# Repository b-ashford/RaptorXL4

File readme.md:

# RaptorXL4  

RaptorXL4 is a custom breakout board I designed to prototype the [Auto-Tuner](https://github.com/b-ashford/Auto-Tuner).  
It’s built around the **STM32L431CBT6** and includes:  

- 24 MHz HSE crystal  
- On-board ST-LINK–compatible programmer/debugger  
- User LED for quick “blinky” tests  
- VDDA supply with ferrite bead filtering for cleaner ADC performance  
- Access to most MCU pins for prototyping  
- Cool raptor silkscreen

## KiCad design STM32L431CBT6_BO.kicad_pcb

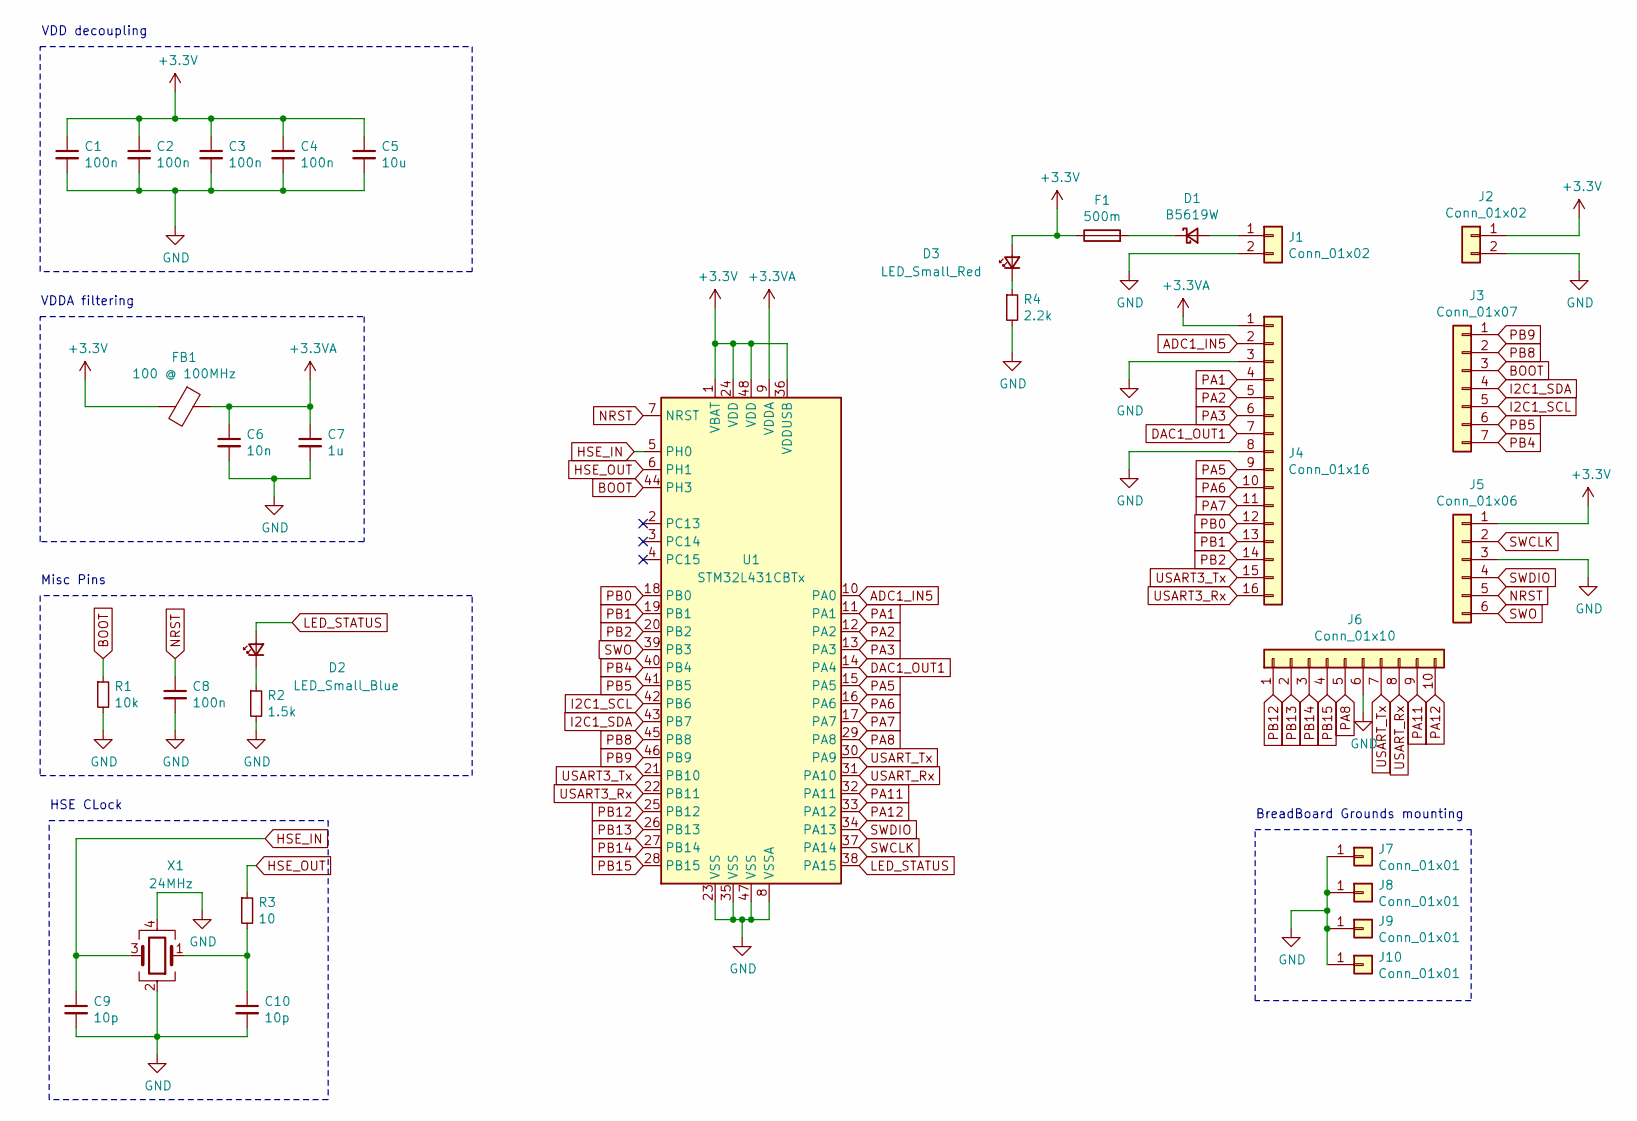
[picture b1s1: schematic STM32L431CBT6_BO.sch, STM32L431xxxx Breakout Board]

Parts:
C1, C2, C3, C4, C8: 100n; C_0402_1005Metric_Pad0.74x0.62mm_HandSolder
C5: 10u; C_0603_1608Metric_Pad1.08x0.95mm_HandSolder
C6: 10n; C_0402_1005Metric_Pad0.74x0.62mm_HandSolder
C7: 1u; C_0603_1608Metric_Pad1.08x0.95mm_HandSolder
C9, C10: 10p; C_0402_1005Metric_Pad0.74x0.62mm_HandSolder
D1: B5619W; D_SOD-123
D2: LED_Small_Blue; LED_0603_1608Metric_Pad1.05x0.95mm_HandSolder
D3: LED_Small_Red; LED_0603_1608Metric_Pad1.05x0.95mm_HandSolder
F1: 500m; Fuse_0603_1608Metric_Pad1.05x0.95mm_HandSolder
FB1: 100 @ 100MHz; L_0805_2012Metric_Pad1.05x1.20mm_HandSolder
J1, J2: Conn_01x02; PinHeader_1x02_P2.54mm_Vertical
J3: Conn_01x07; PinHeader_1x07_P2.54mm_Vertical
J4: Conn_01x16; PinHeader_1x16_P2.54mm_Vertical
J5: Conn_01x06; PinHeader_1x06_P2.54mm_Vertical
J6: Conn_01x10; PinHeader_1x10_P2.54mm_Vertical
J7, J8, J9, J10: Conn_01x01; PinHeader_1x01_P2.54mm_Vertical
R1: 10k; R_0402_1005Metric_Pad0.72x0.64mm_HandSolder
R2: 1.5k; R_0603_1608Metric_Pad0.98x0.95mm_HandSolder
R3: 10; R_0402_1005Metric_Pad0.72x0.64mm_HandSolder
R4: 2.2k; R_0603_1608Metric_Pad0.98x0.95mm_HandSolder
U1: STM32L431CBTx; LQFP-48_7x7mm_P0.5mm
X1: 24MHz; Crystal_SMD_3225-4Pin_3.2x2.5mm_HandSoldering

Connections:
+3.3VA: C6.1, C7.1, FB1.1, J4.1, U1.9 (VDDA)
+3V3: C1.1, C2.1, C3.1, C4.1, C5.1, D3.2 (A), F1.1, FB1.2, J2.1, J5.1, U1.1 (VBAT), U1.24 (VDD), U1.36 (VDDUSB), U1.48 (VDD)
ADC1_IN5: J4.2, U1.10 (PA0)
BOOT: J3.3, R1.1, U1.44 (PH3)
DAC1_OUT1: J4.7, U1.14 (PA4)
GND: C1.2, C2.2, C3.2, C4.2, C5.2, C6.2, C7.2, C8.2, C9.2, C10.2, J1.2, J2.2, J4.3, J4.8, J5.3, J6.6, J7.1, J8.1, J9.1, J10.1, R1.2, R2.2, R4.2, U1.8 (VSSA), U1.23 (VSS), U1.35 (VSS), U1.47 (VSS), X1.2, X1.4
HSE_IN: C9.1, U1.5 (PH0), X1.3
HSE_OUT: R3.1, U1.6 (PH1)
I2C1_SCL: J3.5, U1.42 (PB6)
I2C1_SDA: J3.4, U1.43 (PB7)
LED_STATUS: D2.2 (A), U1.38 (PA15)
NRST: C8.1, J5.5, U1.7 (NRST)
unnamed: C10.1, R3.2, X1.1
unnamed: D1.1 (K), F1.2
unnamed: D1.2 (A), J1.1
unnamed: D2.1 (K), R2.1
unnamed: D3.1 (K), R4.1
PA1: J4.4, U1.11 (PA1)
PA2: J4.5, U1.12 (PA2)
PA3: J4.6, U1.13 (PA3)
PA5: J4.9, U1.15 (PA5)
PA6: J4.10, U1.16 (PA6)
PA7: J4.11, U1.17 (PA7)
PA8: J6.5, U1.29 (PA8)
PA11: J6.9, U1.32 (PA11)
PA12: J6.10, U1.33 (PA12)
PB0: J4.12, U1.18 (PB0)
PB1: J4.13, U1.19 (PB1)
PB2: J4.14, U1.20 (PB2)
PB4: J3.7, U1.40 (PB4)
PB5: J3.6, U1.41 (PB5)
PB8: J3.2, U1.45 (PB8)
PB9: J3.1, U1.46 (PB9)
PB12: J6.1, U1.25 (PB12)
PB13: J6.2, U1.26 (PB13)
PB14: J6.3, U1.27 (PB14)
PB15: J6.4, U1.28 (PB15)
SWCLK: J5.2, U1.37 (PA14)
SWDIO: J5.4, U1.34 (PA13)
SWO: J5.6, U1.39 (PB3)
USART3_Rx: J4.16, U1.22 (PB11)
USART3_Tx: J4.15, U1.21 (PB10)
USART_Rx: J6.8, U1.31 (PA10)
USART_Tx: J6.7, U1.30 (PA9)

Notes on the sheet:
HSE CLock
VDD decoupling
VDDA filtering
Misc Pins
BreadBoard Grounds mounting

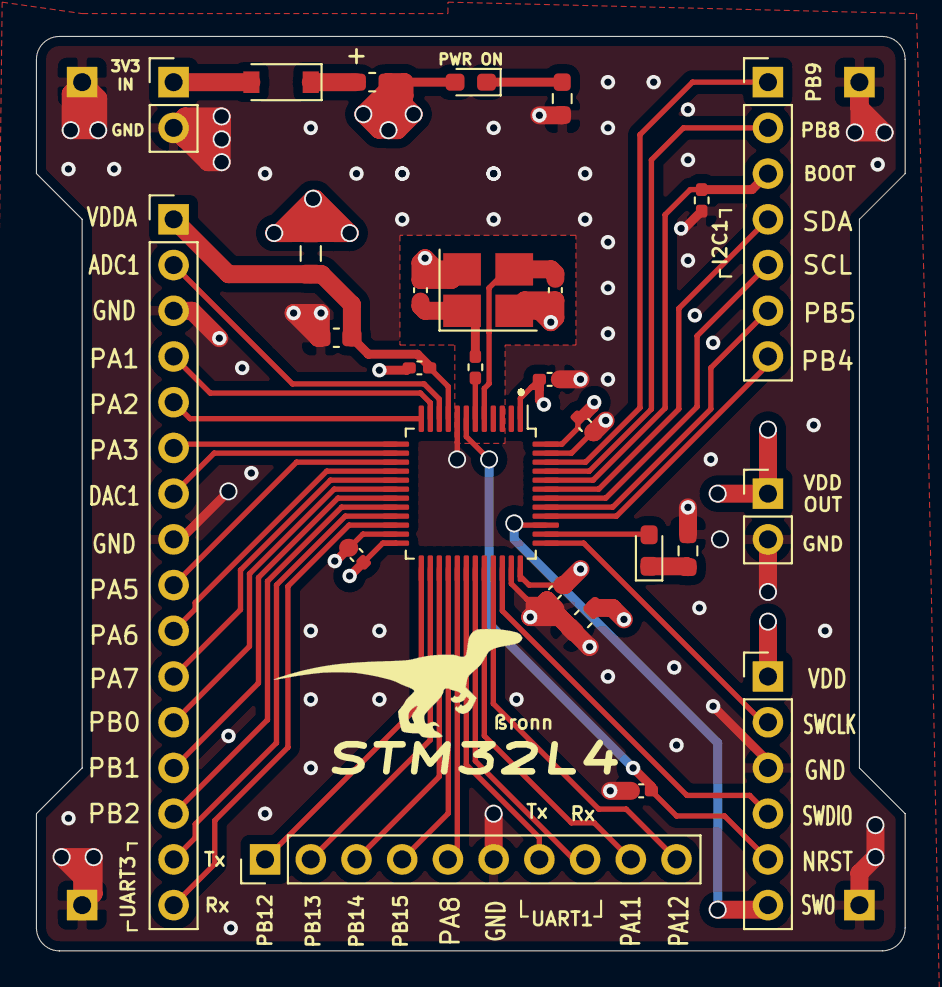
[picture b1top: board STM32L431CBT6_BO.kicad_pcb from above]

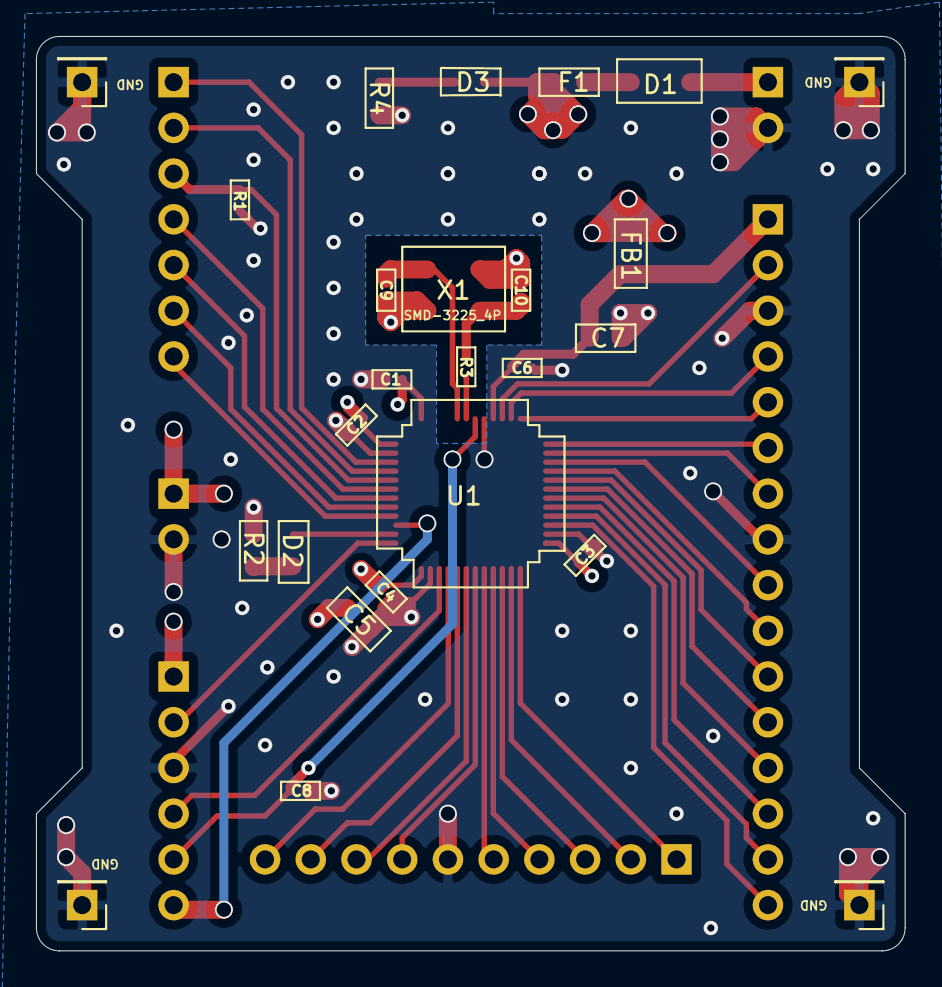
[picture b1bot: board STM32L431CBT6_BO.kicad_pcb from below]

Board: 4 copper layers, 48.3 x 50.8 mm, 31 parts (4 on the bottom side), 44 nets.

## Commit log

2025-08-29 init
2025-08-29 Remove .DS_Store files
2025-08-29 moved
2025-08-29 ignore mac files
2025-08-29 adding readme
